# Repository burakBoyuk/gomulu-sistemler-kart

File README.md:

# Gömülü Sistemler Kartı

YouTube'daki **Gömülü Sistemler** serisinde sıfırdan tasarladığımız ATmega328PB tabanlı, Arduino uyumlu genel amaçlı geliştirme kartı.
Şematikten PCB'ye, üretimden programlamaya kadar her adım seride anlatılıyor.

- Bölümler: [burakkaanboyuk.com/liste.html?k=gomulu-sistemler](https://burakkaanboyuk.com/liste.html?k=gomulu-sistemler)

## Kartta neler var

- **MCU:** ATmega328PB, 16 MHz kristal, Arduino IDE ile programlanabilir
- **Güç:** 5 V giriş, AMS1117-3.3 ile 3,3 V; ters gerilim koruması
- **Giriş / çıkış:** optokuplörlü iki giriş, transistörle sürülen röle çıkışı, fan kontrolü
- **Sensör ve haberleşme:** TMP1075 I²C sıcaklık sensörü, I²C / SPI / programlama konnektörleri; LED'ler ve bir buton

## Klasörler

| Klasör | İçerik |
|---|---|
| `hardware/` | KiCad projesi (şematik, PCB, BOM) |
| `firmware/` | Örnek kodlar (bölümler ilerledikçe) |
| `docs/` | Şematik PDF |

Şematiğin PDF hâli: [`docs/es_brd_v000-schematic.pdf`](docs/es_brd_v000-schematic.pdf).
Gerber ve drill dosyaları depoda tutulmaz; KiCad'de **File → Fabrication Outputs** ile üretilebilir.
Kart revizyonları `rev-vXYZ` etiketleriyle işaretlidir.

## Açmak için

Proje **KiCad 10** ile hazırlandı. Daha eski sürümler dosyaları açamaz; KiCad kurmadan bakmak için şematik PDF'i kullanabilirsiniz.

Tüm semboller ve footprint'ler KiCad'in kendi kütüphanelerinden; ek kütüphane gerekmez.

## Röle çıkışı hakkında

Bu kart eğitim amaçlıdır. Röle çıkışını şebeke gerilimiyle (230 V AC) kullanmadan önce rölenin ve klemensin değerlerini, kart üzerindeki yalıtım mesafelerini kendiniz kontrol edin. Şebeke gerilimiyle çalışmak hayati tehlike taşır.

## Lisans

| Kapsam | Lisans |
|---|---|
| Donanım (`hardware/`) | [CERN-OHL-P-2.0](LICENSE) |
| Yazılım (`firmware/`) | [MIT](LICENSES/MIT.txt) |
| Doküman ve görseller (`docs/`, bu dosya) | [CC BY 4.0](LICENSES/CC-BY-4.0.txt) |

© 2026 Burak Kaan Böyük

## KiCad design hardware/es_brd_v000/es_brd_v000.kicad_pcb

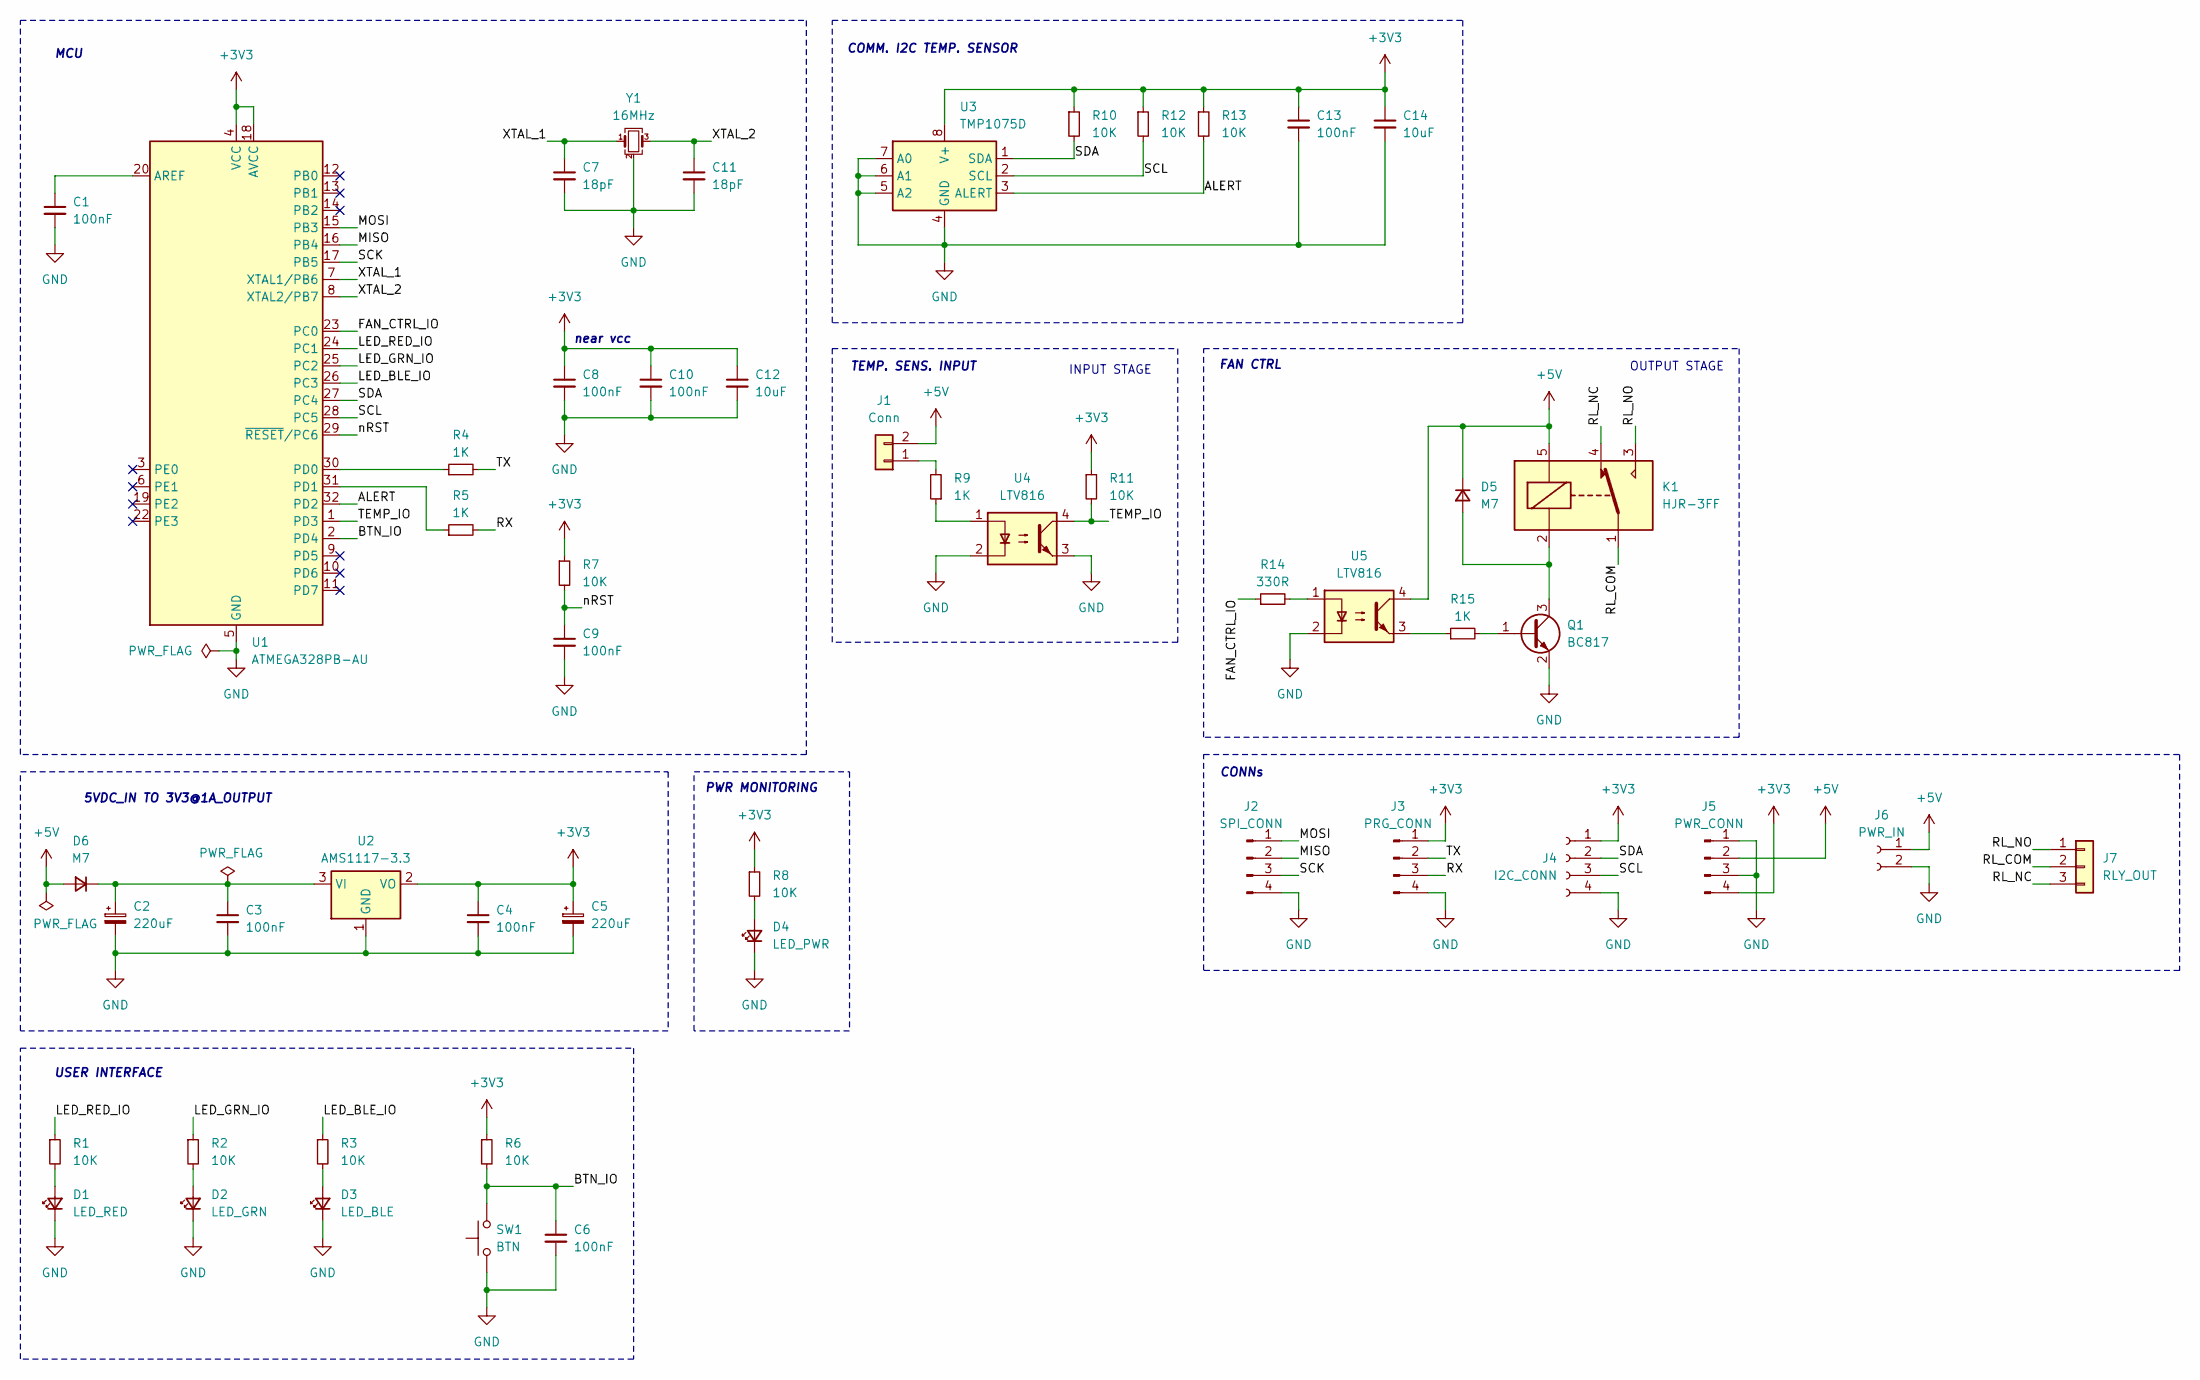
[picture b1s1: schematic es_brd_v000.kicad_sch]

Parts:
C1, C3, C4, C6, C8, C9, C10, C13: 100nF; C_0603_1608Metric
C2, C5: 220uF; CP_Elec_6.3x7.7
C7, C11: 18pF; C_0603_1608Metric
C12, C14: 10uF; C_0603_1608Metric
D1: LED_RED; LED_0603_1608Metric
D2: LED_GRN; LED_0603_1608Metric
D3: LED_BLE; LED_0603_1608Metric
D4: LED_PWR; LED_0603_1608Metric
D5, D6: M7; D_SMA
J1: Conn; JST_XH_B2B-XH-A_1x02_P2.50mm_Vertical
J2: SPI_CONN; PinHeader_1x04_P2.54mm_Vertical
J3: PRG_CONN; PinHeader_1x04_P2.54mm_Vertical
J4: I2C_CONN; JST_XH_B4B-XH-A_1x04_P2.50mm_Vertical
J5: PWR_CONN; PinHeader_1x04_P2.54mm_Vertical
J6: PWR_IN; JST_XH_S2B-XH-A_1x02_P2.50mm_Horizontal
J7: RLY_OUT; PhoenixContact_MSTBA_2,5_3-G-5,08_1x03_P5.08mm_Horizontal
K1: HJR-3FF; Relay_SPDT_SANYOU_SRD_Series_Form_C
Q1: BC817; SOT-23
R1, R2, R3, R6, R7, R8, R10, R11, R12, R13: 10K; R_0603_1608Metric
R4, R5, R9, R15: 1K; R_0603_1608Metric
R14: 330R; R_0603_1608Metric
SW1: BTN; SW_SPST_Omron_B3FS-105xP
U1: ATMEGA328PB-AU; TQFP-32_7x7mm_P0.8mm
U2: AMS1117-3.3; SOT-223-3_TabPin2
U3: TMP1075D; SO-8_3.9x4.9mm_P1.27mm
U4, U5: LTV816; DIP-4_W7.62mm_SMDSocket_SmallPads
Y1: 16MHz; Crystal_SMD_3225-4Pin_3.2x2.5mm

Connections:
+3V3: C4.1, C5.1, C8.1, C10.1, C12.1, C13.1, C14.1, J3.1, J4.1, J5.4, R6.1, R7.1, R8.1, R10.1, R11.1, R12.1, R13.1, U1.4 (VCC), U1.18 (AVCC), U2.2 (VO), U3.8 (V+)
+5V: D5.1 (K), D6.2 (A), J1.2, J5.2, J6.1, K1.5, U5.4
/ALERT: R13.2, U1.32 (PD2), U3.3 (ALERT)
/BTN_IO: C6.1, R6.2, SW1.2, U1.2 (PD4)
/FAN_CTRL_IO: R14.1, U1.23 (PC0)
/LED_BLE_IO: R3.1, U1.26 (PC3)
/LED_GRN_IO: R2.1, U1.25 (PC2)
/LED_RED_IO: R1.1, U1.24 (PC1)
/MISO: J2.2, U1.16 (PB4)
/MOSI: J2.1, U1.15 (PB3)
/RL_COM: J7.2, K1.1
/RL_NC: J7.3, K1.4
/RL_NO: J7.1, K1.3
/RX: J3.3, R5.2
/SCK: J2.3, U1.17 (PB5)
/SCL: J4.3, R12.2, U1.28 (PC5), U3.2 (SCL)
/SDA: J4.2, R10.2, U1.27 (PC4), U3.1 (SDA)
/TEMP_IO: R11.2, U1.1 (PD3), U4.4
/TX: J3.2, R4.2
/XTAL_1: C7.1, U1.7 (XTAL1/PB6), Y1.1
/XTAL_2: C11.1, U1.8 (XTAL2/PB7), Y1.3
/nRST: C9.1, R7.2, U1.29 (~RESET/PC6)
GND: C1.2, C2.2, C3.2, C4.2, C5.2, C6.2, C7.2, C8.2, C9.2, C10.2, C11.2, C12.2, C13.2, C14.2, D1.1 (K), D2.1 (K), D3.1 (K), D4.1 (K), J2.4, J3.4, J4.4, J5.1, J5.3, J6.2, Q1.2 (E), SW1.1, U1.5 (GND), U1.21 (GND), U2.1 (GND), U3.4 (GND), U3.5 (A2), U3.6 (A1), U3.7 (A0), U4.2, U4.3, U5.2, Y1.2 (G), Y1.4 (G)
unnamed: D1.2 (A), R1.2
unnamed: D2.2 (A), R2.2
unnamed: D3.2 (A), R3.2
unnamed: D4.2 (A), R8.2
unnamed: D5.2 (A), K1.2, Q1.3 (C)
unnamed: C2.1, C3.1, D6.1 (K), U2.3 (VI)
unnamed: J1.1, R9.2
unnamed: Q1.1 (B), R15.2
unnamed: R9.1, U4.1
unnamed: R14.2, U5.1
unnamed: R15.1, U5.3
unnamed: C1.1, U1.20 (AREF)
unnamed: R4.1, U1.30 (PD0)
unnamed: R5.1, U1.31 (PD1)

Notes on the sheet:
5VDC_IN TO 3V3@1A_OUTPUT
USER INTERFACE
OUTPUT STAGE
MCU
INPUT STAGE
PWR MONITORING
near vcc
FAN CTRL
COMM. I2C TEMP. SENSOR
TEMP. SENS. INPUT
CONNs

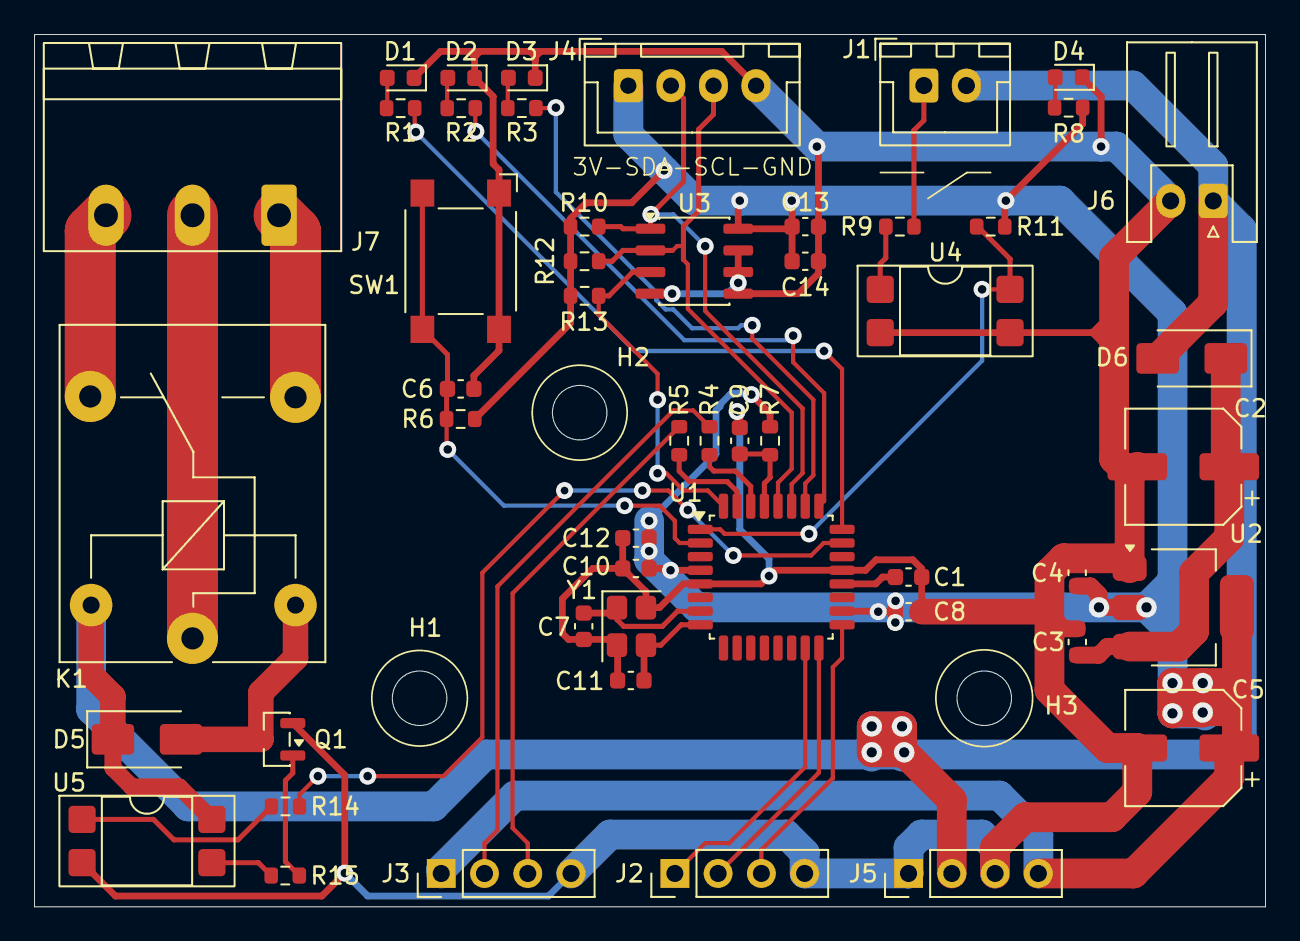
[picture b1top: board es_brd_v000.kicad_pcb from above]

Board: 2 copper layers, 72.3 x 51.2 mm, 51 parts (0 on the bottom side), 37 nets.
